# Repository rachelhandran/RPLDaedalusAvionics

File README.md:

# RPL Daedalus Avionics

5.11.24
Welcome! This is my guide for the RPL Daedalus Project Avionics, in particular, the software and PCB files I designed and used on my rocket during the 2022-2023 cohort.
I used an Arduino Nano to drive 2 sensors, a pressure/altitude/temperature sensor (BMP388), and an IMU/gyroscope/accelerometer/magnetometer (BNO055). The system also includes an SD Card and Module, and a battery. The code written is designed to read pressure/temp/altitude, IMU data, and write it to the SD Card.

The PCB Files are attached, I designed in Eagle. Feel free to copy and edit these files to add or remove any functionalities.

See my latest version and updates below.

## v2/IMUFlightComp.ino
5.20.23 

This is the newest flight computer software that interfaces with the PCB v2.0. It has support for BMP388 temperature, pressure, and altitude sensing, as well as IMU 9DoF Raw Data: Accelerometer, Gyroscope, and Magnetometer data. The software reads all the above data, including IMU calibration status data, and writes them to the SD card in CSV format.

CSV format:
*Temperature (C), Pressure (hPa), Altitude (m), IMU Calibration (System), IMU Calibration (Accelerometer), IMU Calibration (Gyroscope), IMU Calibration (Magnetometer), Accel_X (m/s^2), Accel_Y (m/s^2), Accel_Z (m/s^2), Gyro_X (rad/s), Gyro_Y (rad/s), Gyro_Z(rad/s), Mag_X (uT), Mag_Y (uT), Mag_Z (uT)*

This version of code also supports a Piezo buzzer (but the PCB does not have a spot for the buzzer, this code can only be used on a system designed with a buzzer.) This version plays a constant buzz to inform that data is successfully reading and writing to SD. If not buzzing, the SD Card is likely not initialized properly. Eject and re-enter, and click RESET on the Arduino. Continue until the buzz begins.

## Hardware Setup
5.21.23

## PCB v2.0
5.6.23

3D Views:

Board: 

Schematic: 

## v1.0

This is the flight computer for our NMP Avionics system. 

*The software is designed for BMP388 only. Software is not necessarily compatible for BMP280. Hardware IS compatible with both, but you must write your own code to call the BMP280 library instead of the BMP388.*

`flightComputer.ino` is the flight program. Once uploaded, there will be a 5s delay, then the BMP388 sensor will read in temp, pressure, and altitude data, and write to a file in the SD card once every 100ms.

`flightCompDebug.ino` is outdated. It was a duplicate sandbox code to practice and debug. 

### Hardware/PCB v1 Setup:

Ensure the BMP388 and BMP280 are wired/soldered to the PCB correctly. 
On the PCB, GND is the 2nd pin from the right. Match the GND pin of your component (BMP280) and the GND pin on the PCB when orienting your components to ensure functionality.

## Procedure (BMP388 only):
1. Solder PCB components: Arduino Nano, BMP388, SD Card Module, and battery. Ensure you have a new battery. Keep battery OFF. Mount an SD Card.
2. Download flightComputer.ino to your Arduino IDE.
3. Edit flightComputer.ino to Arduino Nano. For testing, ensure number in the filename in line 164 is 100+. If flying, change number to 1-99. This helps for post-processing to distinguish the correct data.
4. Upload your version of flightComputer.ino to the Nano thru USB cable. Check serial monitor to ensure valid output stream. Unplug the cable, now you have successfully uploaded the program and will supply power from now on through the battery pack.
5. Mount the avionics bay in your rocket. When flight time comes, turn on the battery pack. Remember, after 5s, the program will begin. It will end when it loses power or runs out of memory. (Battery goes out much quicker (~10h) than filling up 32GB of storage with plain text, see notes.)
6. Recover the rocket and turn OFF the switch. Read from SD Card for data analysis.

# Notes:
## Memory
How long will it take to fill a 32gb SD card with this data (25 bytes per line)?
- In CSV file, 25 chars = 25 bytes per line
	- 25 bytes / 0.1 second
	- 250 bytes / 1 second
	- 15,000 bytes / 1 min
	- 900,000 bytes / 1 hour
	- 21,600,000 / 24hrs or 1 day
- 32GB = 32,000,000,000 bytes
- It will take 35,555 hours or 1481 days to fill the SD Card at a rate of 25 bytes / sec and 32GB storage

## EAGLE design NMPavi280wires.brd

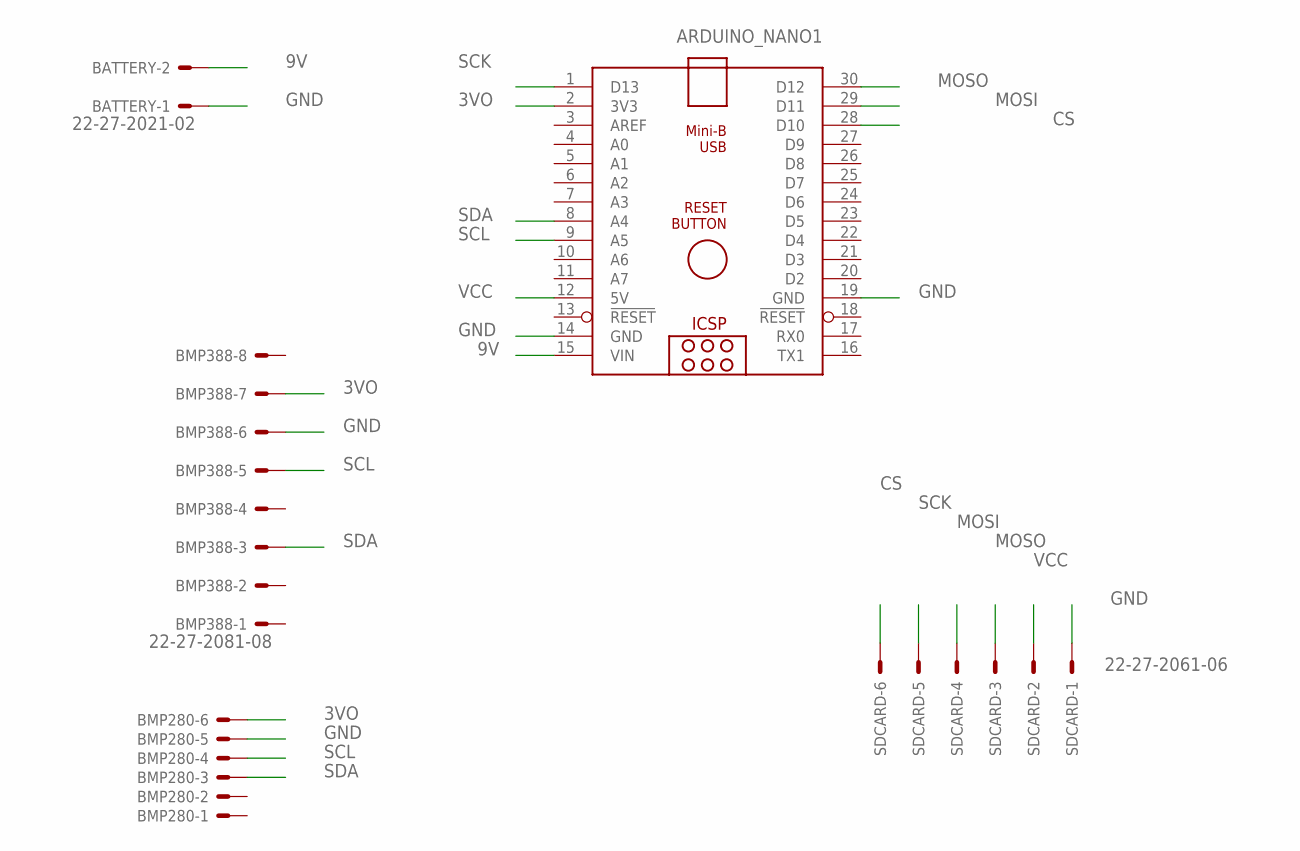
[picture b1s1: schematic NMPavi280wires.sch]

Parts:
ARDUINO_NANO1: ARDUINO_NANO
BATTERY: 22-27-2021-02; 6410-02
BMP280: 22-23-2061
BMP388: 22-27-2081-08; 6410-08
SDCARD: 22-27-2061-06; 6410-06

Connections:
3VO: ARDUINO_NANO1.2 (3V3), BMP280.6, BMP388.7
9V: ARDUINO_NANO1.15 (VIN), BATTERY.2
CS: ARDUINO_NANO1.28 (D10), SDCARD.6
GND: ARDUINO_NANO1.14 (GND), ARDUINO_NANO1.19 (GND), BATTERY.1, BMP280.5, BMP388.6, SDCARD.1
MOSI: ARDUINO_NANO1.29 (D11), SDCARD.4
MOSO: ARDUINO_NANO1.30 (D12), SDCARD.3
SCK: ARDUINO_NANO1.1 (D13), SDCARD.5
SCL: ARDUINO_NANO1.9 (A5), BMP280.4, BMP388.5
SDA: ARDUINO_NANO1.8 (A4), BMP280.3, BMP388.3
VCC: ARDUINO_NANO1.12 (5V), SDCARD.2

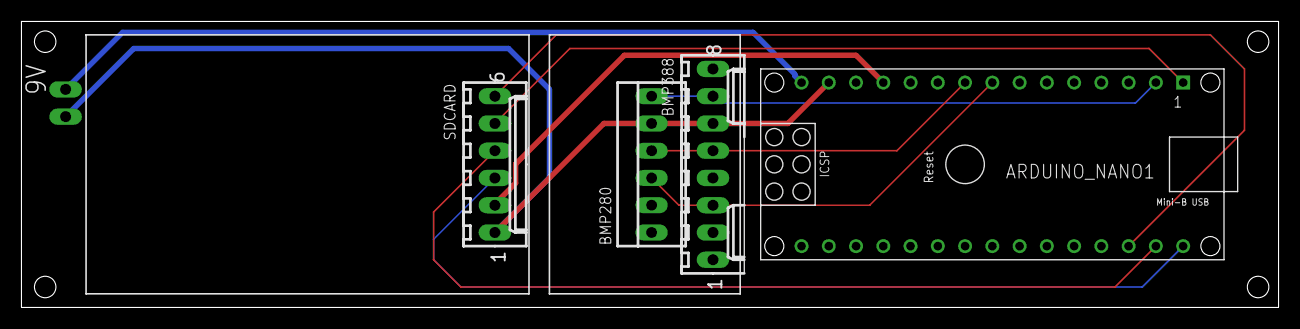
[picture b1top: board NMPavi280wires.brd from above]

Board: 2 copper layers, 117.1 x 26.7 mm, 5 parts (1 on the bottom side), 10 nets.

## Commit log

2023-02-25 v1.0
    Complete working version of NMP flight computer.
    10s delay at start,
    Reads sensor data from BMP388 and stores to SD card every second.
2023-02-25 Add files via upload
    flightCompDebug is a duplicate of the flightComputer file and acts as a sandbox. No writing functionality is built into the loop.
2023-04-18 NMP avionics board, schematic, and gerber files
2023-04-29 Update flightComputer.ino
    Use this version, not the debug file
2023-04-29 Add files via upload
    Images of how to orient the BMP280
2023-04-30 Moved all images into img
2023-05-07 uploaded new schematic, brd, gerber files, and updated imgs
2023-05-07 moved files to v1 and v2 folders
2023-05-20 Update IMUFlightComp.ino
    Printing raw data directly to the SD card. Previous code attempted to convert data into string and print, wich caused problems.
2023-05-20 Update IMUFlightComp.ino
    IMU data prints to serial and SD card in CSV format
2023-05-20 Update IMUFlightComp.ino
    Successful BMP and IMU data to serial monitor AND sd card in CSV format!
2023-05-20 Update IMUFlightComp.ino
    Deleted unnecessary helper functions.
2023-05-20 Update IMUFlightComp.ino
    Added piezo buzzer
2023-05-21 Update IMUFlightComp.ino
    Added debug if statement
2023-05-21 updated readme with pictures
2023-05-22 Revert IMUFlightComp.ino to no buzzer
    No buzzer
2023-05-22 Added if statement for FLIGHT, changed text file to FLIGHT.txt
